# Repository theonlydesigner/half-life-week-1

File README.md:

# week 1: rp2040 dev board & mini hackpad

## project goals
* **Target Specs:** custom RP2040 microcontroller board using the QFN-56 package, 16MB QSPI flash, 12MHz crystal oscillator, USB-C connector with 5.1k CC pull-down resistors, and dual-row breakout headers for all GPIO pins to drive a mini hackpad.
* **Design Philosophy:** build a functional dev board from absolute ground zero using the hack club stasis guide so i finally understand what goes on under the hood of a raspberry pi pico [instead of treating microcontrollers like magic black boxes].
* **Why I'm building this:** week 1 theme is PCB, and i needed a custom board to integrate with an old mini hackpad design i had lying around. also i wanted to suffer through routing 0402 passives and tiny IC pins.

## bill of materials (BOM)
* refer to `bom.csv` in this folder for the full list of parts including the RP2040 MCU, W25Q128 flash chip, LDO voltage regulator, buttons, and passive components.

## dev journal - part 6: left-side GPIO routing (the lost footage)
* **Time spent:** 2 hours
* **Recorded on lapse:** no [because my brain shut off and i forgot to hit record]

this was easily the most painful part of the entire week. of course, this is the exact 2-hour block where i forgot to start the lapse recording, so you'll just have to take my word for it that i was working and not staring blankly at a wall.

since this was my first time designing an RP2040 board from scratch, trying to connect the RP2040 pins to the left-side GPIO headers turned into a complete trace-routing nightmare. i was following the hack club stasis guide (`stasis.hackclub.com/starter-projects/devboard`), but making clean connections for GPIO0 through GPIO15 without crossing traces or creating illegal angles felt like playing a high-stakes game of snake. 

i had to pause every 5 minutes to watch multiple youtube tutorials on KiCad trace routing, net classes, and how to use vias without making the PCB look like cheese. i kept triggering Design Rule Check (DRC) errors because my traces were either too close to the ground plane or running over decoupling capacitors. after two hours of tearing my hair out, re-routing lines three times over, and wrestling with via placements, the left side is finally connected and fully routed. 

## visual showcase

*(the fully routed RP2040 dev board before sending it off to the fab house)*

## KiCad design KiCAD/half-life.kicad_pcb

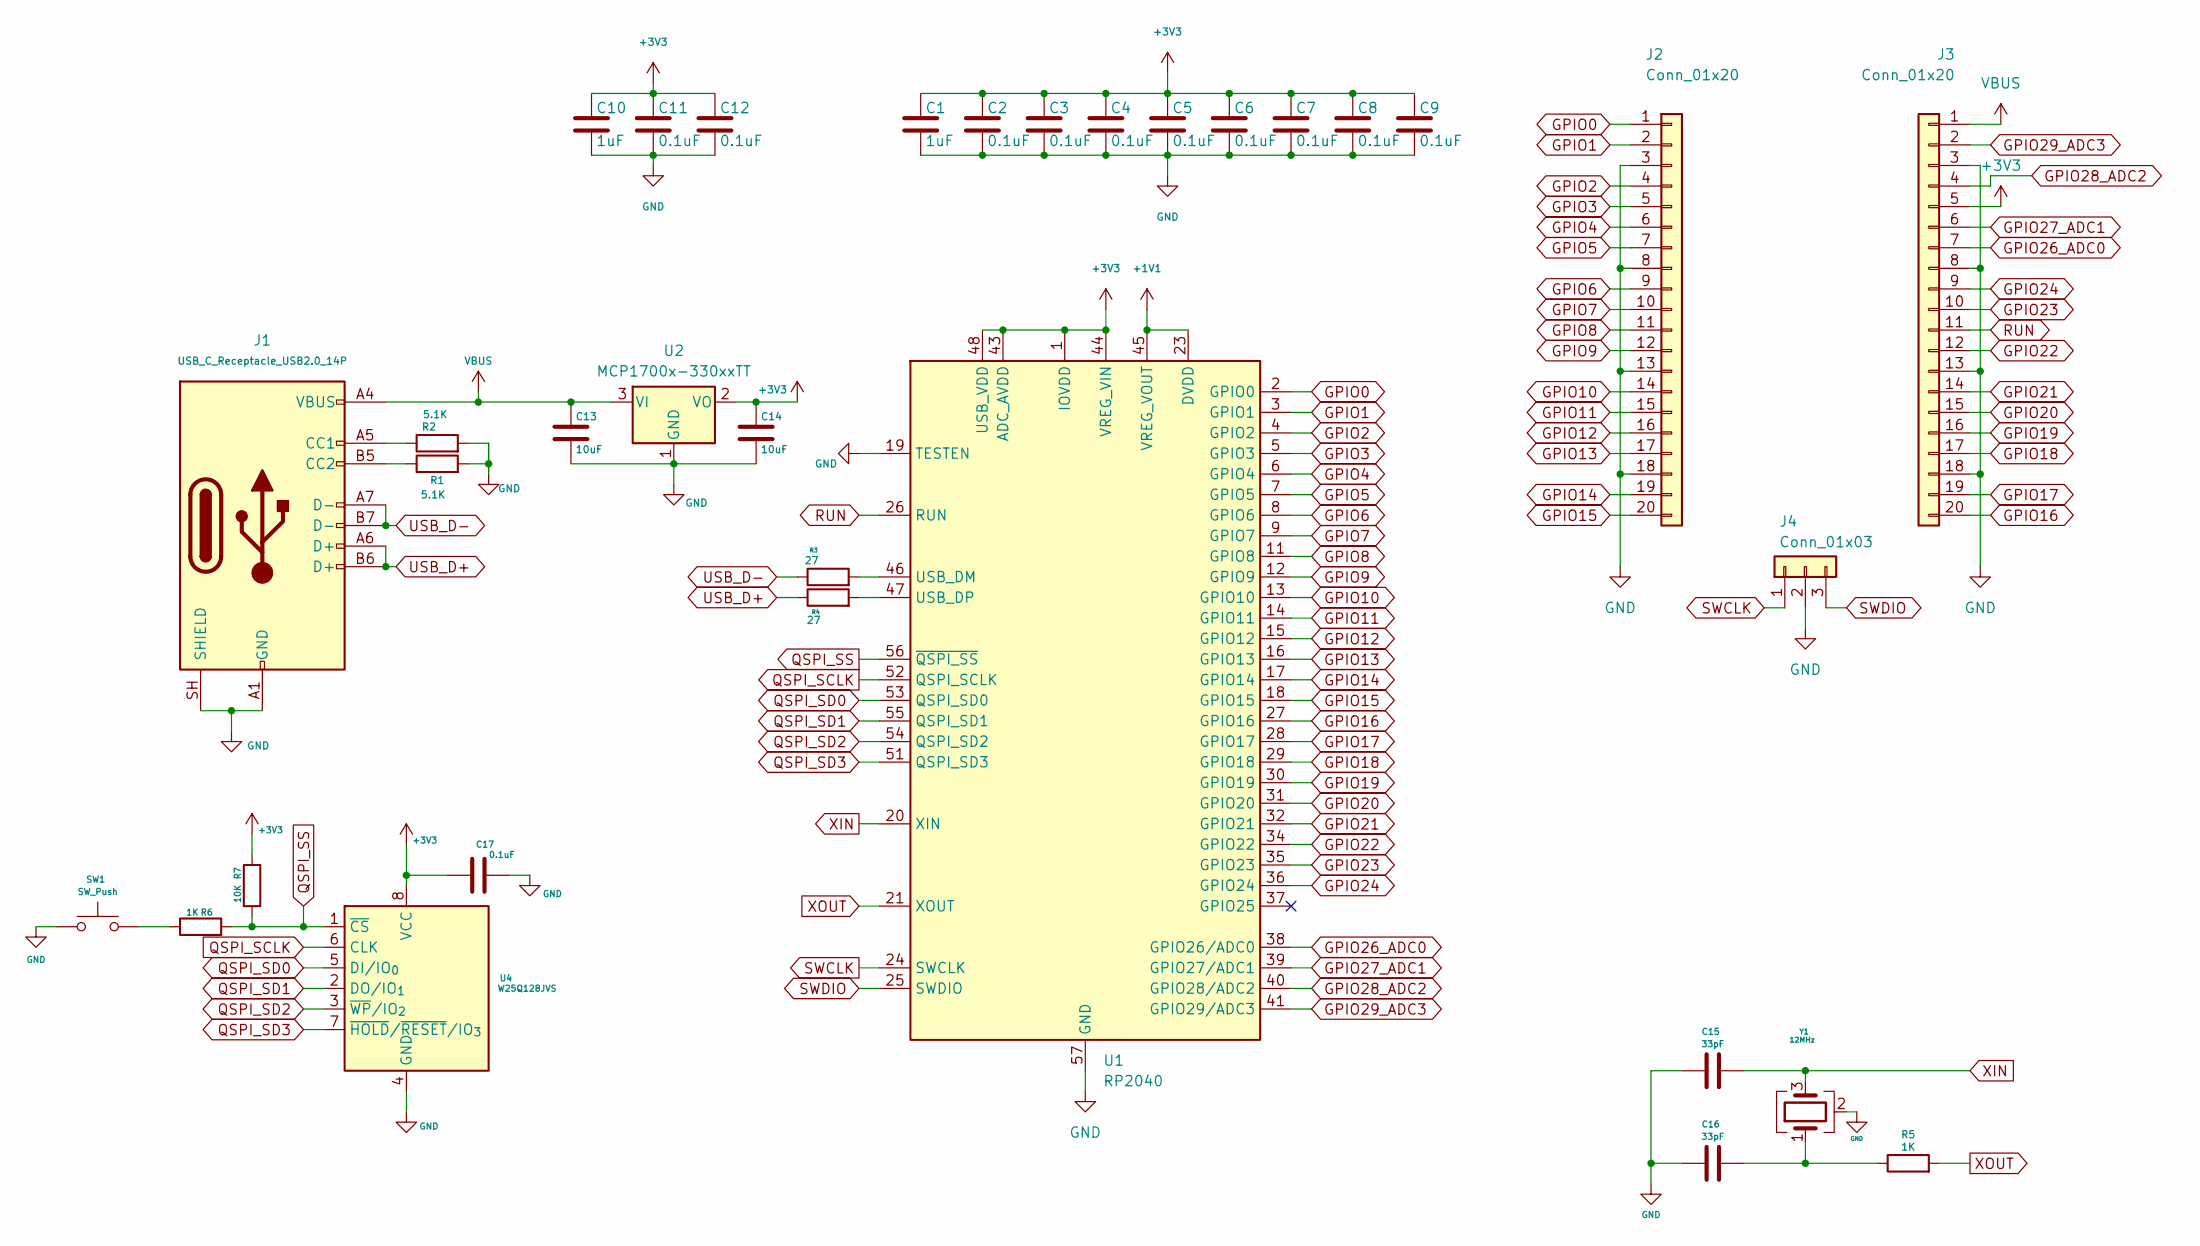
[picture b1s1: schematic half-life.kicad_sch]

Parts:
C1, C10: 1uF; C_0402_1005Metric
C2, C3, C4, C5, C6, C7, C8, C9, C11, C12, C17: 0.1uF; C_0402_1005Metric
C13, C14: 10uF; C_0603_1608Metric
C15, C16: 33pF; C_0603_1608Metric
J1: USB_C_Receptacle_USB2.0_14P; USB_C_Receptacle_HRO_TYPE-C-31-M-12
J2, J3: Conn_01x20; PinHeader_1x20_P2.54mm_Vertical
J4: Conn_01x03; PinHeader_1x03_P2.54mm_Vertical
R1, R2: 5.1K; R_0402_1005Metric
R3, R4: 27; R_0402_1005Metric
R5, R6: 1K; R_0402_1005Metric
R7: 10K; R_0402_1005Metric
SW1: SW_Push; SW_Push_SPST_NO_Alps_SKRK
U1: RP2040; QFN-56-1EP_7x7mm_P0.4mm_EP3.2x3.2mm
U2: MCP1700x-330xxTT; SOT-23
U4: W25Q128JVS; Winbond_USON-8-1EP_3x2mm_P0.5mm_EP0.2x1.6mm
Y1: 12MHz; Crystal_SMD_3225-4Pin_3.2x2.5mm

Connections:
+1V1: U1.23 (DVDD), U1.45 (VREG_VOUT), U1.50 (DVDD)
+3V3: C1.1, C2.1, C3.1, C4.1, C5.1, C6.1, C7.1, C8.1, C9.1, C10.1, C11.1, C12.1, C14.1, C17.1, J3.5, R7.2, U1.1 (IOVDD), U1.10 (IOVDD), U1.22 (IOVDD), U1.33 (IOVDD), U1.42 (IOVDD), U1.43 (ADC_AVDD), U1.44 (VREG_VIN), U1.48 (USB_VDD), U1.49 (IOVDD), U2.2 (VO), U4.8 (VCC)
GND: C1.2, C2.2, C3.2, C4.2, C5.2, C6.2, C7.2, C8.2, C9.2, C10.2, C11.2, C12.2, C13.2, C14.2, C15.1, C16.1, C17.2, J1.A1 (GND), J1.A12 (GND), J1.B1 (GND), J1.B12 (GND), J1.SH (SHIELD), J2.3, J2.8, J2.13, J2.18, J3.3, J3.8, J3.13, J3.18, J4.2, R1.2, R2.2, SW1.1, U1.19 (TESTEN), U1.57 (GND), U2.1 (GND), U4.4 (GND), Y1.2 (G), Y1.4 (G)
GPIO0: J2.1, U1.2 (GPIO0)
GPIO1: J2.2, U1.3 (GPIO1)
GPIO2: J2.4, U1.4 (GPIO2)
GPIO3: J2.5, U1.5 (GPIO3)
GPIO4: J2.6, U1.6 (GPIO4)
GPIO5: J2.7, U1.7 (GPIO5)
GPIO6: J2.9, U1.8 (GPIO6)
GPIO7: J2.10, U1.9 (GPIO7)
GPIO8: J2.11, U1.11 (GPIO8)
GPIO9: J2.12, U1.12 (GPIO9)
GPIO10: J2.14, U1.13 (GPIO10)
GPIO11: J2.15, U1.14 (GPIO11)
GPIO12: J2.16, U1.15 (GPIO12)
GPIO13: J2.17, U1.16 (GPIO13)
GPIO14: J2.19, U1.17 (GPIO14)
GPIO15: J2.20, U1.18 (GPIO15)
GPIO16: J3.20, U1.27 (GPIO16)
GPIO17: J3.19, U1.28 (GPIO17)
GPIO18: J3.17, U1.29 (GPIO18)
GPIO19: J3.16, U1.30 (GPIO19)
GPIO20: J3.15, U1.31 (GPIO20)
GPIO21: J3.14, U1.32 (GPIO21)
GPIO22: J3.12, U1.34 (GPIO22)
GPIO23: J3.10, U1.35 (GPIO23)
GPIO24: J3.9, U1.36 (GPIO24)
GPIO26_ADC0: J3.7, U1.38 (GPIO26/ADC0)
GPIO27_ADC1: J3.6, U1.39 (GPIO27/ADC1)
GPIO28_ADC2: J3.4, U1.40 (GPIO28/ADC2)
GPIO29_ADC3: J3.2, U1.41 (GPIO29/ADC3)
unnamed: C16.2, R5.1, Y1.1
unnamed: J1.A5 (CC1), R2.1
unnamed: J1.B5 (CC2), R1.1
unnamed: R6.1, SW1.2
unnamed: R3.2, U1.46 (USB_DM)
unnamed: R4.2, U1.47 (USB_DP)
QSPI_SCLK: U1.52 (QSPI_SCLK), U4.6 (CLK)
QSPI_SD0: U1.53 (QSPI_SD0), U4.5 (DI/IO_{0})
QSPI_SD1: U1.55 (QSPI_SD1), U4.2 (DO/IO_{1})
QSPI_SD2: U1.54 (QSPI_SD2), U4.3 (~WP/IO_{2})
QSPI_SD3: U1.51 (QSPI_SD3), U4.7 (~HOLD/~RESET/IO_{3})
QSPI_SS: R6.2, R7.1, U1.56 (~QSPI_SS), U4.1 (~CS)
RUN: J3.11, U1.26 (RUN)
SWCLK: J4.1, U1.24 (SWCLK)
SWDIO: J4.3, U1.25 (SWDIO)
USB_D+: J1.A6 (D+), J1.B6 (D+), R4.1
USB_D-: J1.A7 (D-), J1.B7 (D-), R3.1
VBUS: C13.1, J1.A4 (VBUS), J1.A9 (VBUS), J1.B4 (VBUS), J1.B9 (VBUS), J3.1, U2.3 (VI)
XIN: C15.2, U1.20 (XIN), Y1.3
XOUT: R5.2, U1.21 (XOUT)

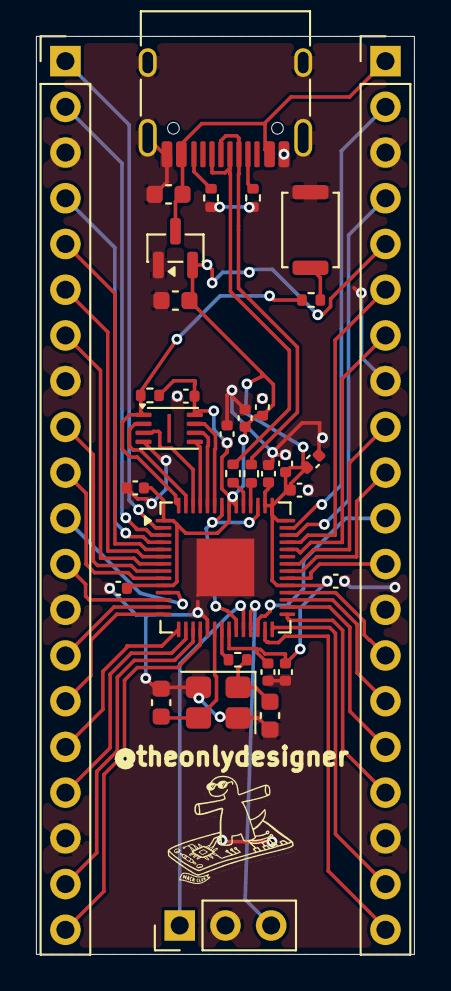
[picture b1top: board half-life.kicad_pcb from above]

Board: 2 copper layers, 21.0 x 51.0 mm, 33 parts (0 on the bottom side), 52 nets.

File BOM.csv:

Part,Quantity,Price,Total Price(With Shipping),
1uF Capacitor,2,0.1,0.1,
0.1uF Capacitor,11,0.1,0.1,
10uF Capacitor,2,0.1,0.1,
33pF Capacitor,2,0.2,0.2,
USB_C_Receptacle_USB2.0_14P,1,0.3,0.3,
Conn_01x20,2,0.6,0.6,
Conn_01x03,1,0.16,0.16,
5.1K Resistor,2,0.1,0.1,
27 Resistor,2,0.1,0.1,
1K Resistor,2,0.1,0.1,
10K Resistor,1,0.1,0.1,
SW_Push,1,0.11,0.11,
RP2040 Chip,1,0.84,1.3,
MCP1700x-330xxTT,1,0.5,0.5,
W25Q128JVS,1,5.02,5.02,
12MHz Crystal,1,0.39,0.39,
PCB w/ Stencil,1,9.3,23,
Solder Paste,1,2.3,3,
Tweezers,1,1.8,1.8,
Cherry MX Switches,16,15.3,15.3,
1N4148 Diodes,16,0.5,0.5,
Wire,1,0.1,0.1,
Screws,4,0.12,,
Keycaps,15,5.8,7,
Solder Iron and stuff related to that,1,3.2,3.2,
Copper Wire for Matrix,1,0.14,0.14,
3D print of case from printing-legion(Top and Bottom counts as one,1,3,7,
,,,,
,,,,
,,,Total Cost:,Rounded:
,,,70.32,75
